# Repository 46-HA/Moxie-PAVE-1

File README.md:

Moxie-PAVE-1

What we’re detecting:
- CO2 Leaks
- Allergens in the air (Mold, pet dander, things found in the spring time, such as pollen)
- VOCs (Volatile Organic Compounds)
- Particulate Matter
- Radon
- Etc

Moxie’s preventions:
- Liver and kidney damage (VOCs)
- Central nervous system damage (VOCs)
- Lung cancer (Particulate matter)
- Asphyxiation (CO2 leaks)
- Cardiovascular disease (Particulate matter)
- Chronic Bronchitis (Particulate matter)
- Increased cancer risk (Radon and VOCs)
- Respiratory irritation (VOCs, particulate matter, and radon)
- Asthma (Allergens and particulate matter)
- Headaches, drowsiness, etc (CO2 leaks)

People at risk:

CO2
- Poorly ventilated places (think schools, offices, basements)
- Infants and elderly (more sensitive to oxygen deprivation)
- People with heart or lung condition
- Low-income households (older houses tend to have worse ventilation or no CO2 monitors)

Allergens
- Children younger adults (likely to develop asthma)
- People w/ allergies or asthma
- High pollen areas

VOCs
- Elderly and children/infants (higher risk of disease)
- Pregnant women (developmental effects in fetuses)
- New homes (exposure to paint/new things) 
- Low-income renters/homes (more VOC-emitting materials)

Particulate Matter
- Elderly people and children/infants
- People with pre-existing diseases/symptoms such as asthma, COPD, or heart disease 
- Urban residents (more exposure from traffic, industry, smoke, etc
- Low-income neighborhoods
- Outdoor workers 

Radon
- Radon-prone regions
- People who live in basements
- Long-term residents (risk builds with exposure time)
- Smokers

Primary groups:
- Children/Infants
- Elderly
- Low-income families
- Urban/Rural/Suburban
- People with pre-existing symptoms (asthma, COPD, etc)
- Smokers
- Workers in certain jobs

Sensor:
SEN55-SDN-T
Datasheet
Cost: $28

Detects:
- NOx
- VOC
- PM
- Humidity
- Temp.

Display:
MDOB048064AV-WI
Datasheet
Cost: $8

Microcontroller:
ESP32-C3FH4
Datasheet
Cost: $2

Battery TBD  

Speaker TBD

Connecting to phone?

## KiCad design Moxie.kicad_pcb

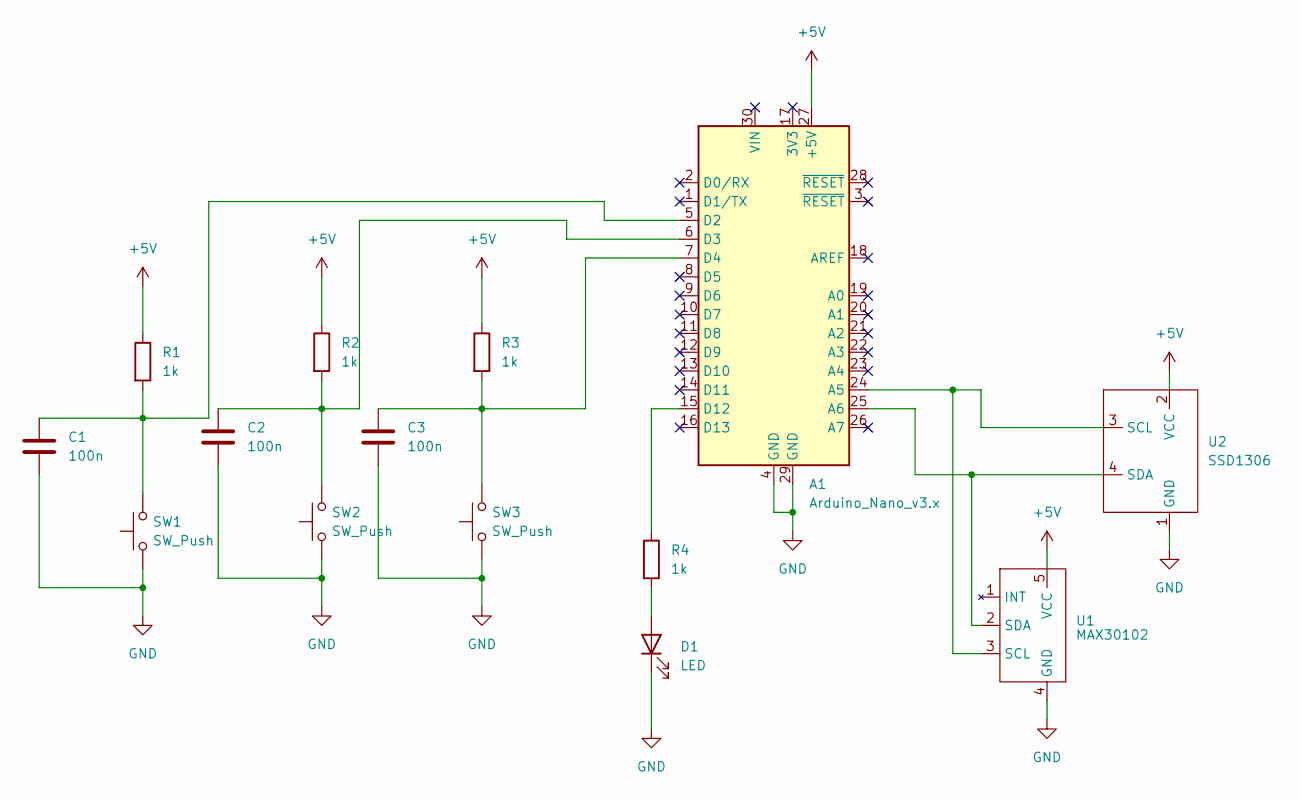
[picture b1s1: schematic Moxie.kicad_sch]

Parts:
A1: Arduino_Nano_v3.x; Arduino_Nano
C1, C2, C3: 100n; C_Disc_D7.0mm_W2.5mm_P5.00mm
D1: LED; LED_D5.0mm
R1, R2, R3, R4: 1k; R_Axial_DIN0207_L6.3mm_D2.5mm_P7.62mm_Horizontal
SW1, SW2, SW3: SW_Push; SW_PUSH_6mm
U1: MAX30102; MAX30102_MODULE
U2: SSD1306

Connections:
+5V: A1.27 (+5V), R1.1, R2.1, R3.1, U1.5 (VCC), U2.2 (VCC)
GND: A1.4 (GND), A1.29 (GND), C1.2, C2.2, C3.2, D1.1 (K), SW1.1, SW2.1, SW3.1, U1.4 (GND), U2.1 (GND)
unnamed: A1.24 (A5), U1.3 (SCL), U2.3 (SCL)
unnamed: A1.25 (A6), U1.2 (SDA), U2.4 (SDA)
unnamed: A1.5 (D2), C1.1, R1.2, SW1.2
unnamed: A1.6 (D3), C2.1, R2.2, SW2.2
unnamed: A1.7 (D4), C3.1, R3.2, SW3.2
unnamed: A1.15 (D12), R4.1
unnamed: D1.2 (A), R4.2

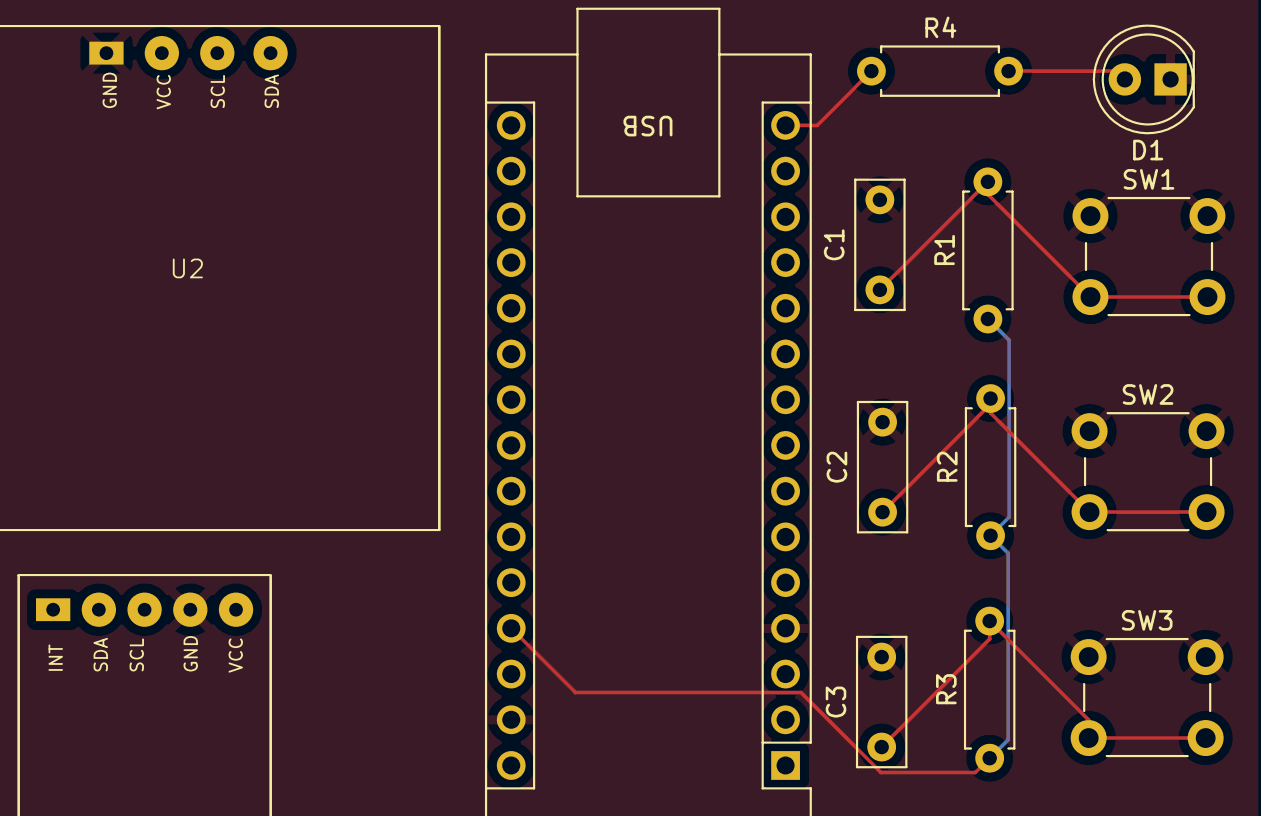
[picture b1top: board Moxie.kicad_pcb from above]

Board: 4 copper layers, 14 parts (0 on the bottom side), 9 nets.

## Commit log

2025-06-29 testing github desktop
2025-06-29 set up kicad and added arduino
2025-06-30 added max30102
2025-06-30 added SDD1306
2025-06-30 ERC check
2025-06-30 added parts
2025-07-01 custom footprints
2025-07-01 custom footprint for MAX30102
2025-07-01 added pins
    fixed an issue with through-hole on kicad and added the 5 pins for the MAX30102 module
2025-07-01 SSD1306 + assigned footprint
2025-07-02 added JLCPCB's rules
2025-07-02 layed out the PCB and filled the copper layer
2025-07-02 routing
2025-07-03 README.md
2025-07-05 footprints
